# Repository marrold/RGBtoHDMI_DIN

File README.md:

# RGBtoHDMI_DIN

A PCB to breakout the RGB DIN connector for use with an RGBtoHDMI converter

**Note:** It's currently untested

## License

- This project is licensed under the MIT license

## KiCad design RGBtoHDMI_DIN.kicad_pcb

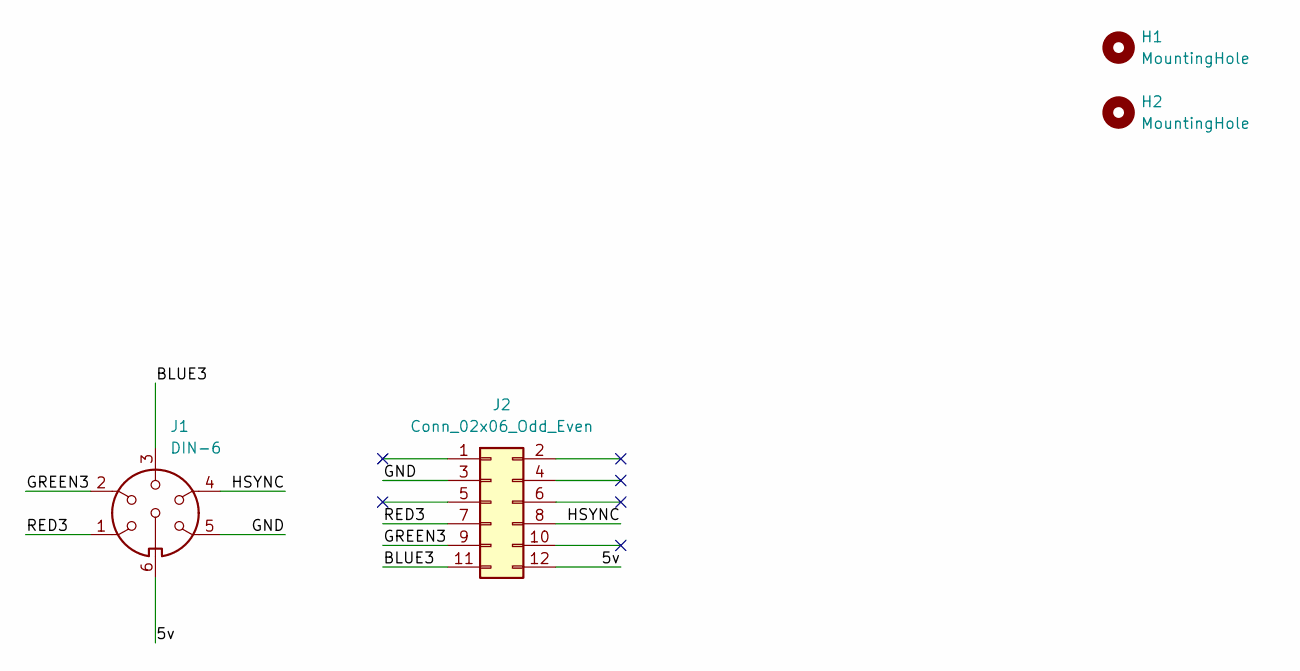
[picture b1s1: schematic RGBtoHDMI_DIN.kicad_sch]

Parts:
H1, H2: MountingHole; MountingHole_3.2mm_M3
J1: DIN-6; DIN6
J2: Conn_02x06_Odd_Even; PinHeader_2x06_P2.54mm_Vertical

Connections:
/5v: J1.6, J2.12
/BLUE3: J1.3, J2.11
/GND: J1.5, J2.3
/GREEN3: J1.2, J2.9
/HSYNC: J1.4, J2.8
/RED3: J1.1, J2.7

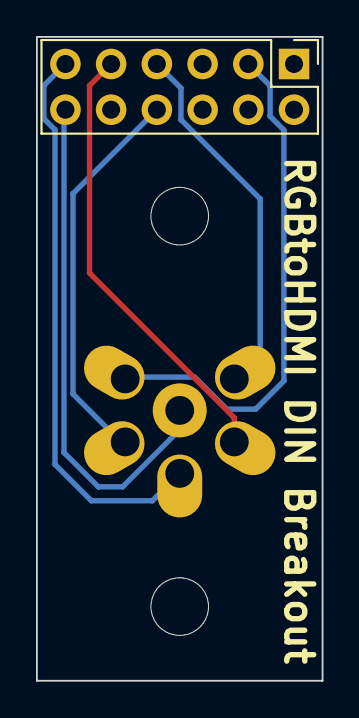
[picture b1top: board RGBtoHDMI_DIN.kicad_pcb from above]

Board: 2 copper layers, 15.9 x 35.8 mm, 4 parts (1 on the bottom side), 6 nets.

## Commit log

2024-01-24 init
